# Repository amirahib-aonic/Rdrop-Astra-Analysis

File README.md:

# Rdrop Astra analysis

Three-stage illustrated evaluation: functional review, conservative refinement and complete redesign.

Website: https://amirahib-aonic.github.io/Rdrop-Astra-Analysis/

The four HTML pages use assets/, sources/ and downloads/. Original individual reports are retained in GPT6 Refined/Comparison/ and GPT6 New/Report/.

Hardware files are prototype evidence; automated design checks do not establish flight, functional or thermal qualification.

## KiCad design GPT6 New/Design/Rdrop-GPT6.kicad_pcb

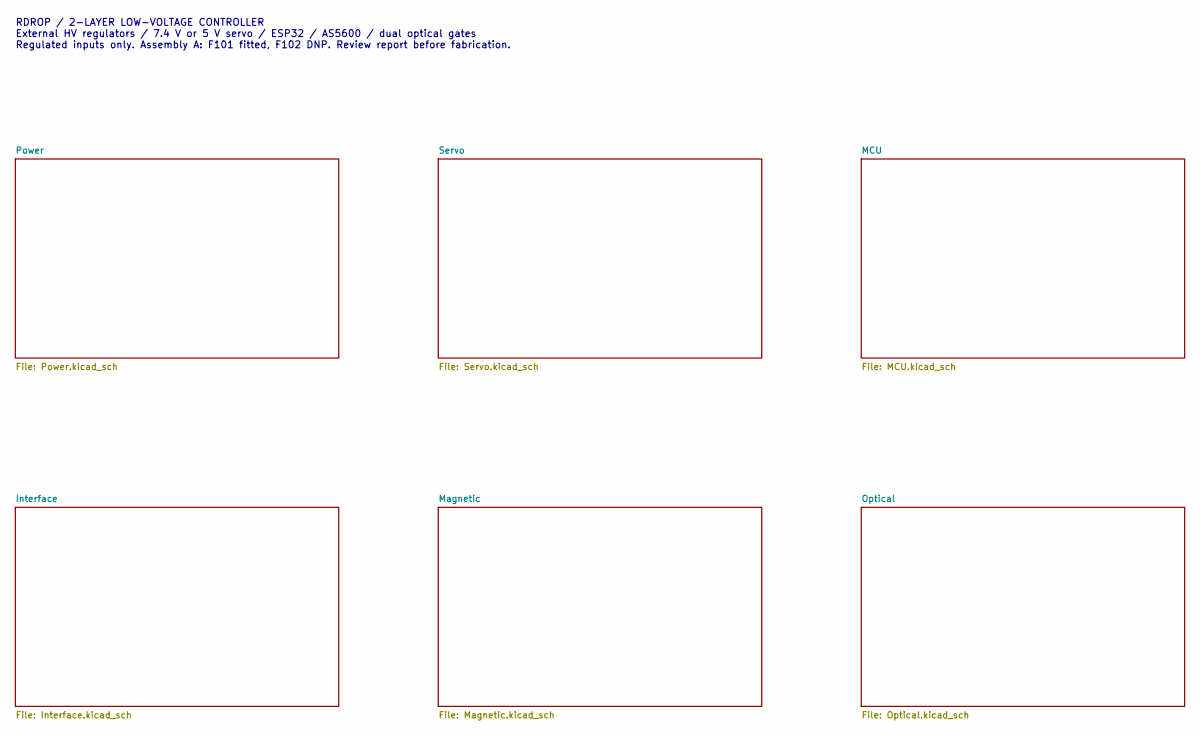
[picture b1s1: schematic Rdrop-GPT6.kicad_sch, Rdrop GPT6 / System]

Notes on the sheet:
RDROP / 2-LAYER LOW-VOLTAGE CONTROLLER External HV regulators / 7.4 V or 5 V servo / ESP32 / AS5600 / dual optical gates Regulated inputs only. Assembly A: F101 fitted, F102 DNP. Review report before fabrication.

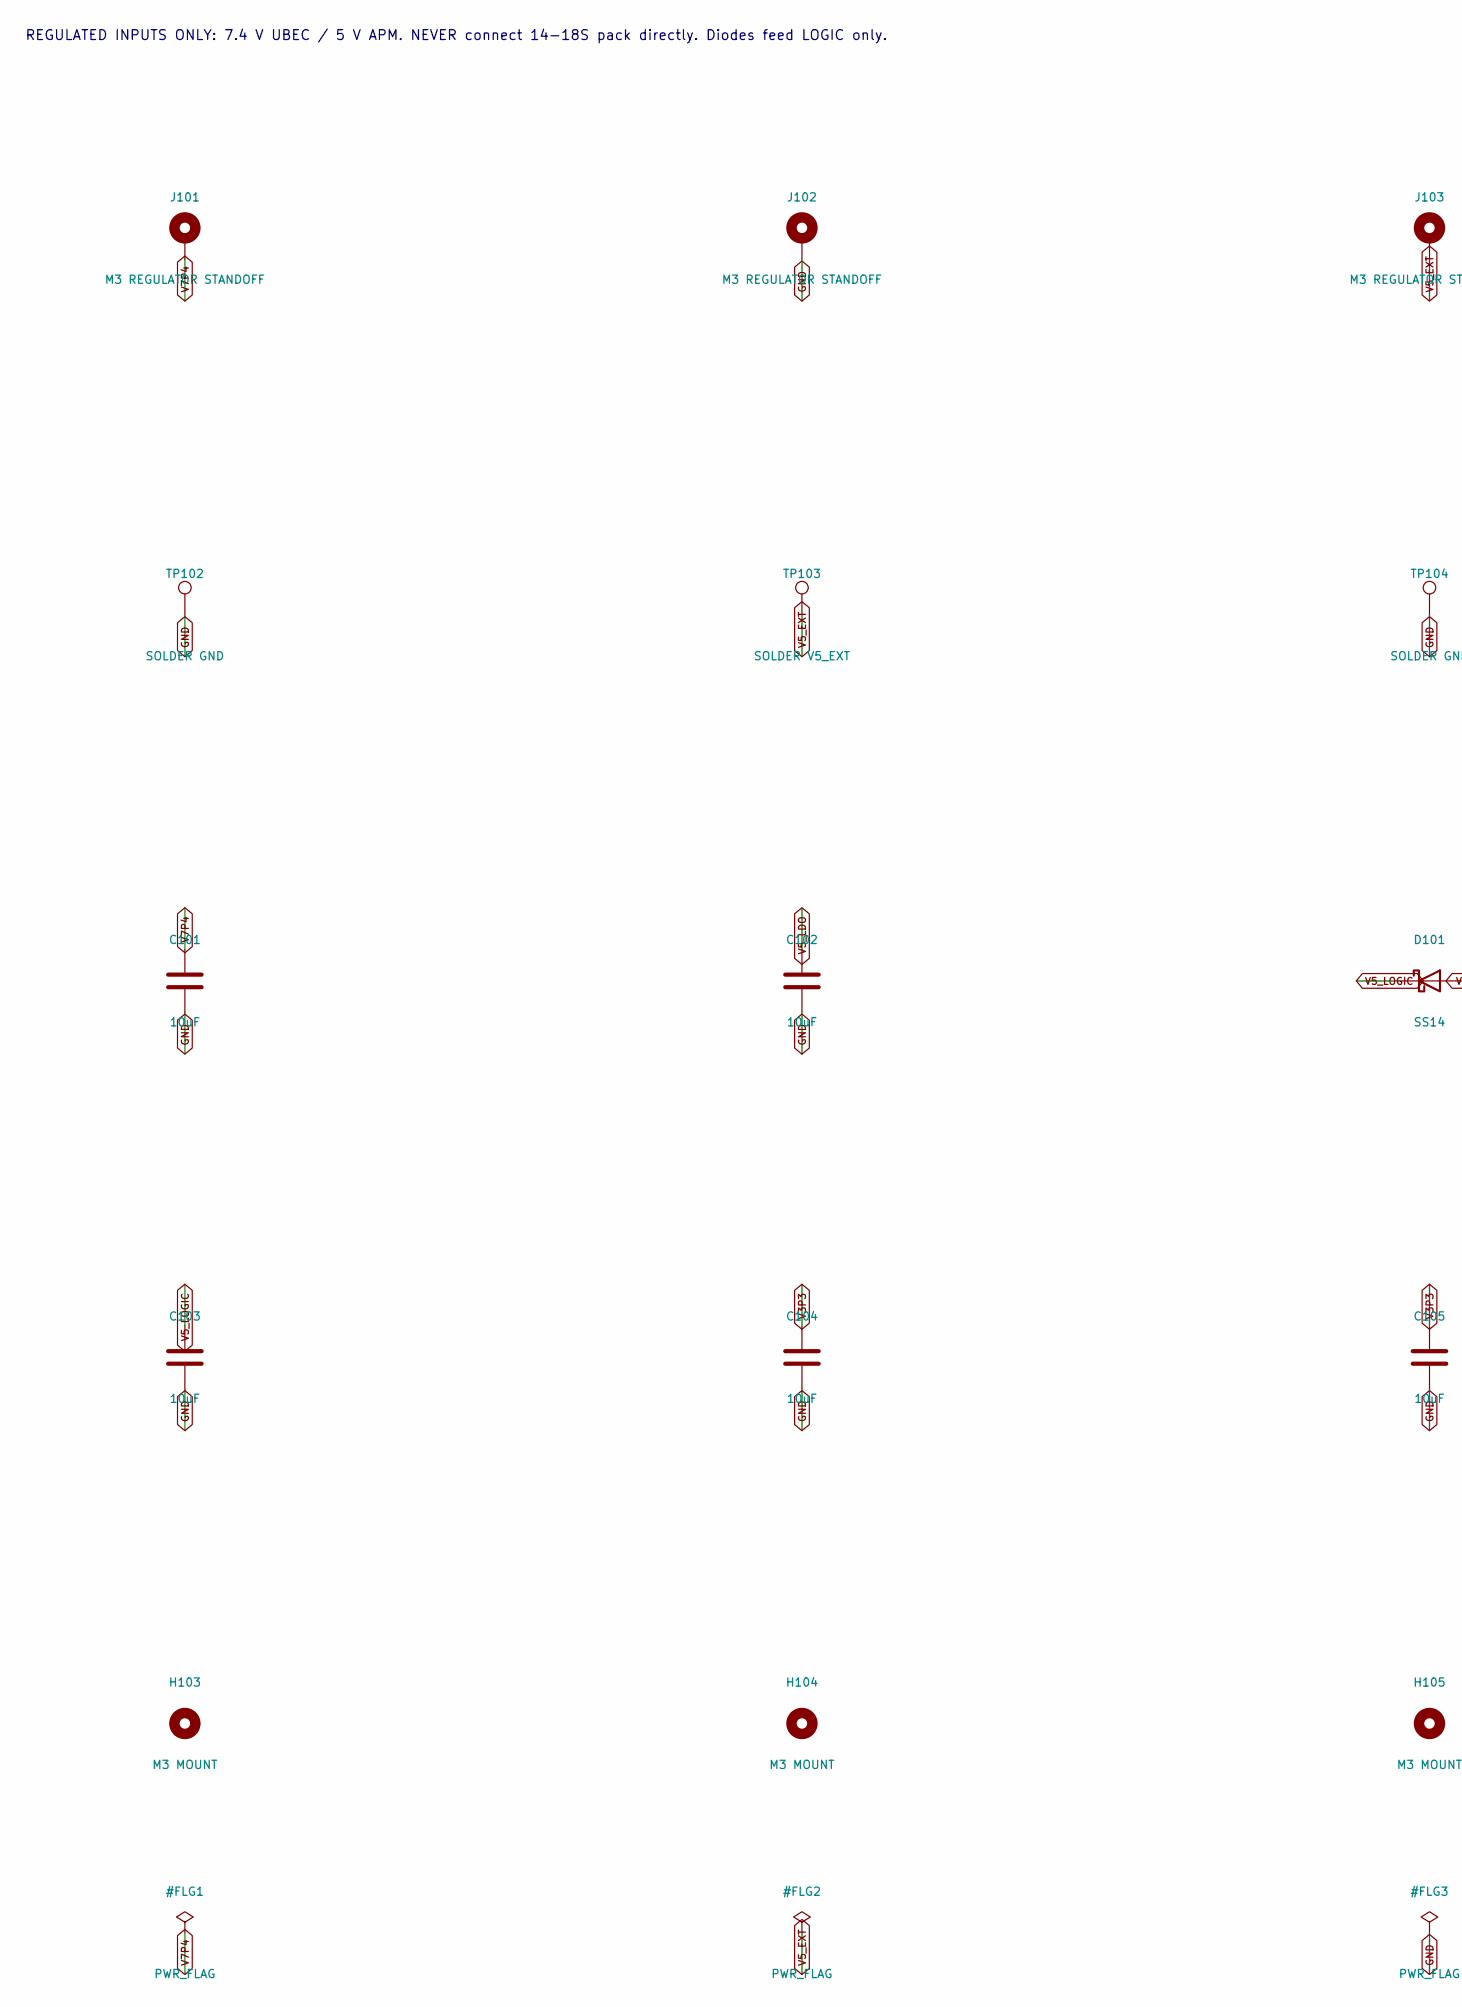
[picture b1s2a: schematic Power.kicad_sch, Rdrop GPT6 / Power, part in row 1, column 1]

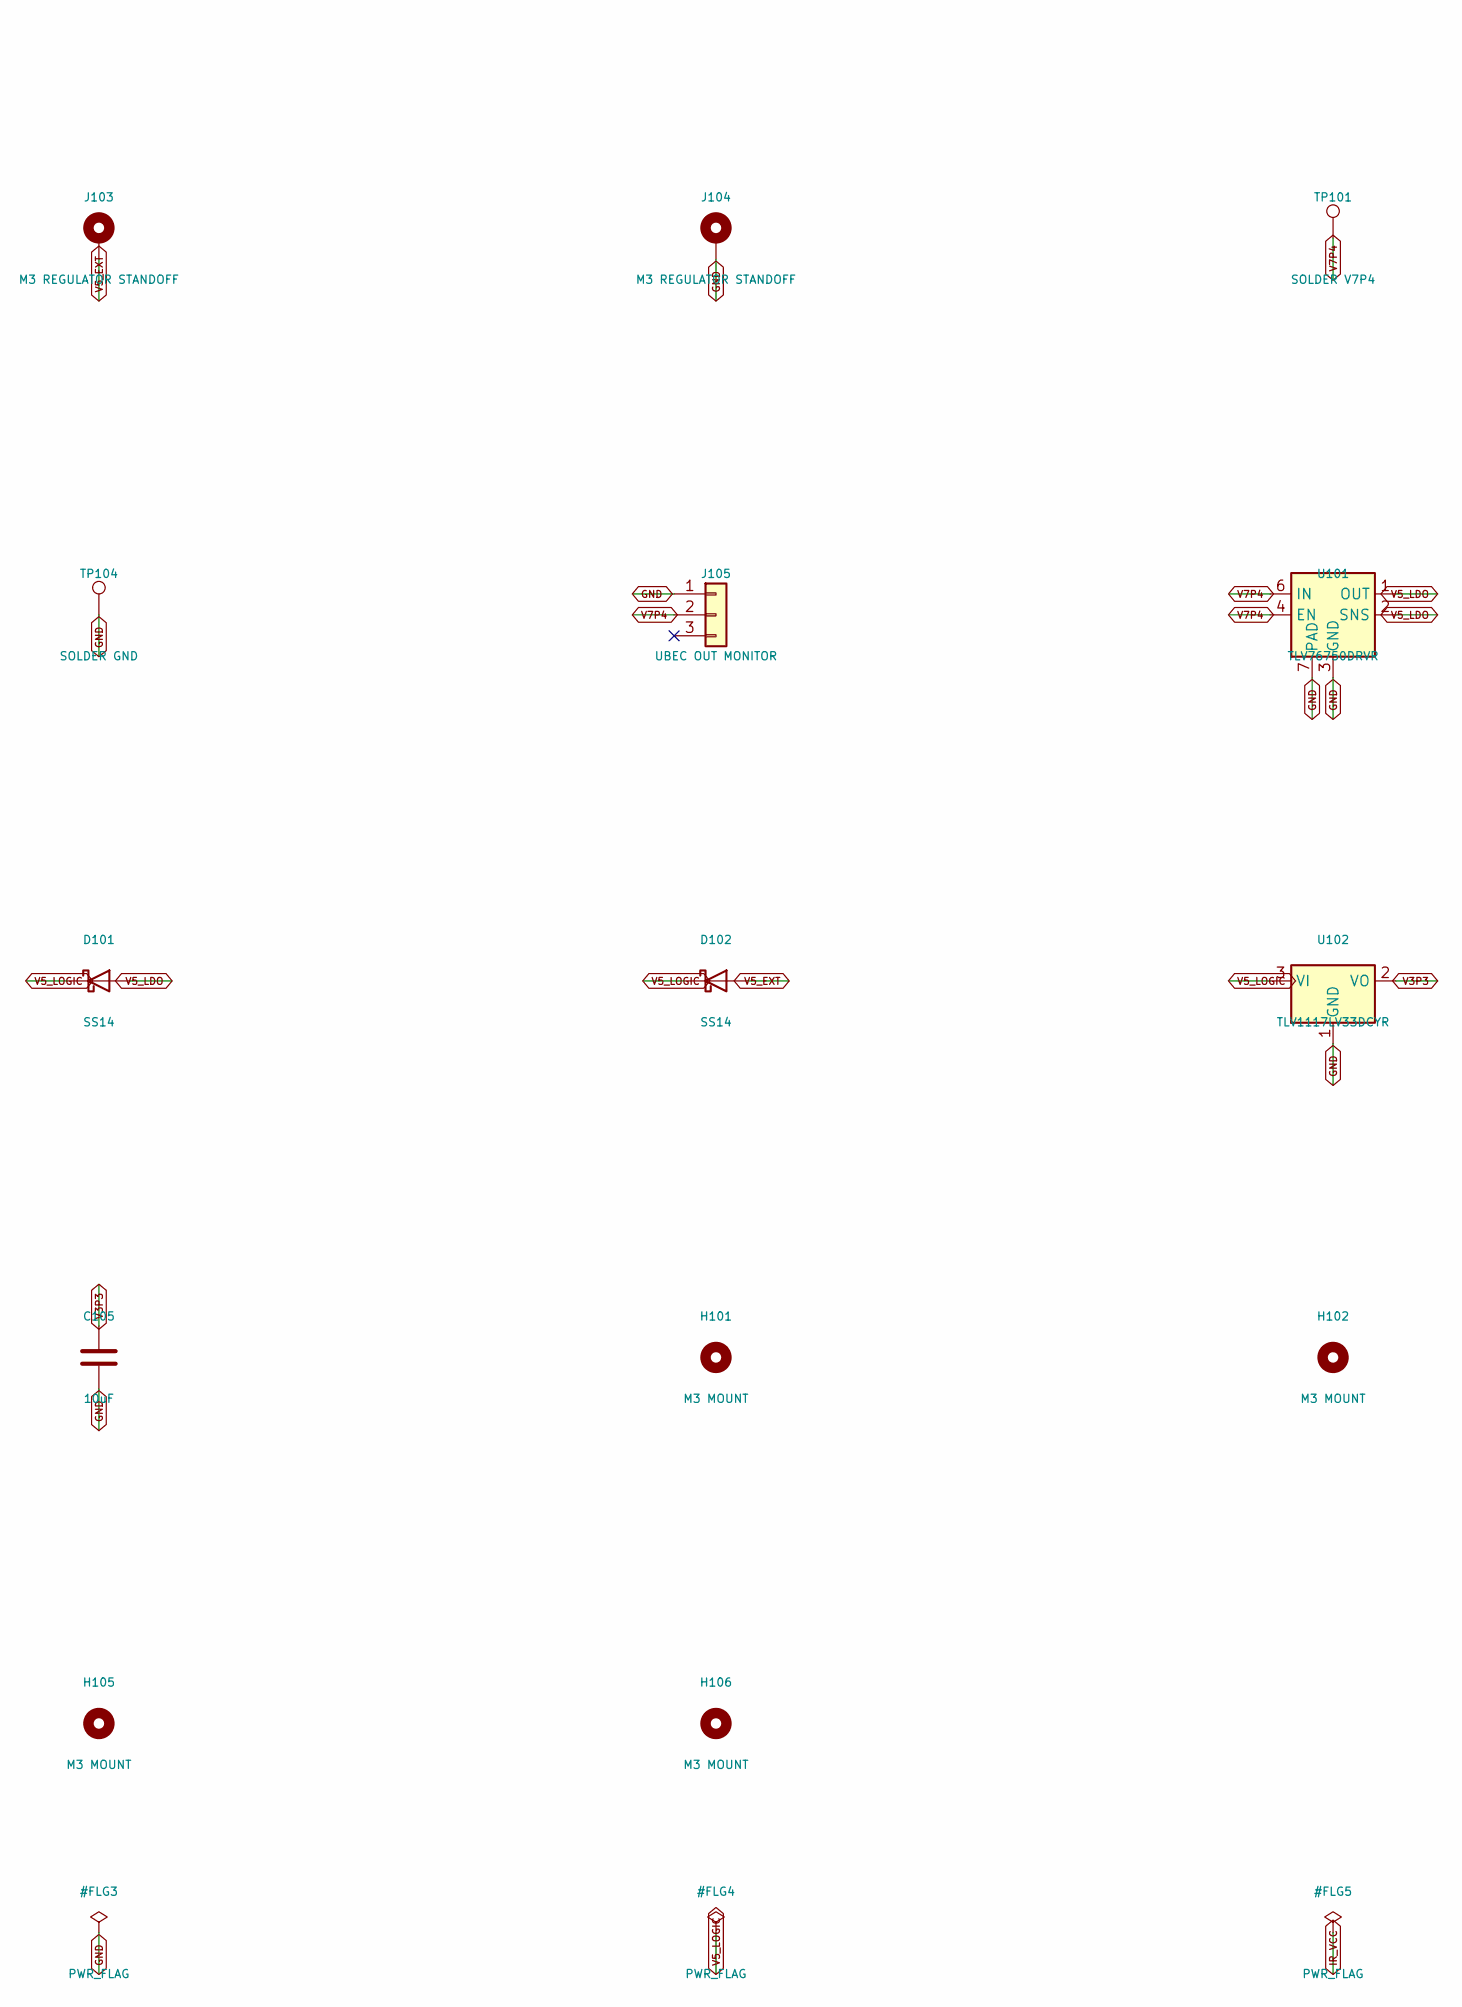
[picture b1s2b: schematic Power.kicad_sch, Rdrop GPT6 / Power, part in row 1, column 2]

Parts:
C101, C102, C103, C104, C105: 10uF; C_0603_1608Metric; MPN GRM188R61C106KAALD
D101, D102: SS14; D_SMA; MPN SS14-E3/61T
H101, H102, H103, H104, H105, H106: M3 MOUNT; MountingHole_3.2mm_M3; MPN M3_HARDWARE
J101, J102, J103, J104: M3 REGULATOR STANDOFF; Mounting_Wuerth_WA-SMSI-M3_H10mm_9774100360; MPN 9774100360R
J105: UBEC OUT MONITOR; PinHeader_1x03_P2.54mm_Vertical; MPN TSW-103-07-G-S
TP101: SOLDER V7P4; TestPoint_Pad_D4.0mm; MPN WIRE_PAD
TP102, TP104: SOLDER GND; TestPoint_Pad_D4.0mm; MPN WIRE_PAD
TP103: SOLDER V5_EXT; TestPoint_Pad_D4.0mm; MPN WIRE_PAD
U101: TLV76750DRVR; WSON-6-1EP_2x2mm_P0.65mm_EP1x1.6mm_ThermalVias; MPN TLV76750DRVR
U102: TLV1117LV33DCYR; SOT-223-3_TabPin2; MPN TLV1117LV33DCYR

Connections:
GND: C101.2, C102.2, C103.2, C104.2, C105.2, J102.1, J104.1, J105.1, TP102.1, TP104.1, U101.3 (GND), U101.5 (GND), U101.7 (PAD), U102.1 (GND); also elsewhere on the board
V3P3: C104.1, C105.1, U102.2 (VO); also elsewhere on the board
V5_EXT: D102.2 (A), J103.1, TP103.1; also elsewhere on the board
V5_LDO: C102.1, D101.2 (A), U101.1 (OUT), U101.2 (SNS)
V5_LOGIC: C103.1, D101.1 (K), D102.1 (K), U102.3 (VI)
V7P4: C101.1, J101.1, J105.2, TP101.1, U101.4 (EN), U101.6 (IN); also elsewhere on the board

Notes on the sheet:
REGULATED INPUTS ONLY: 7.4 V UBEC / 5 V APM. NEVER connect 14-18S pack directly. Diodes feed LOGIC only.

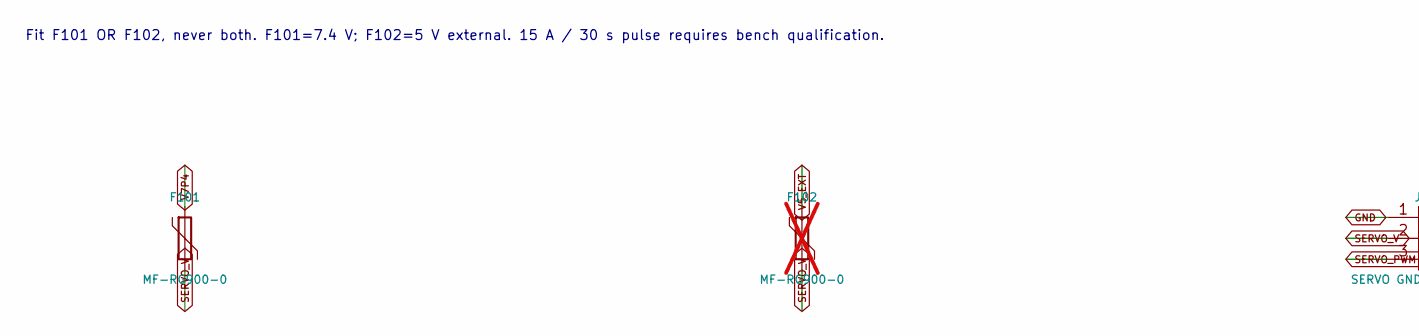
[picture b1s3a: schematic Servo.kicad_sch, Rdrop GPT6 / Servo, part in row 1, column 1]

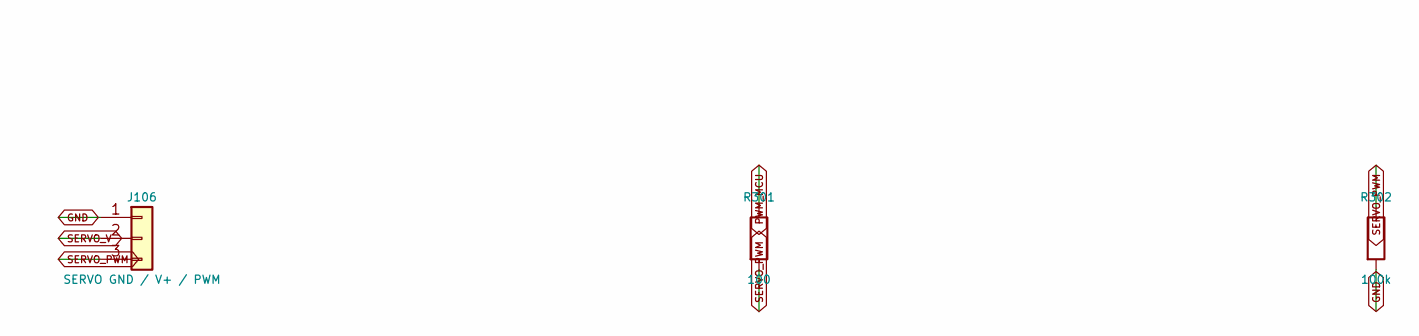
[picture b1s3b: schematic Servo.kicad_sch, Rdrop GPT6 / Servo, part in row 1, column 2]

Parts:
F101: MF-RG900-0; Fuse_Bourns_MF-RG900; MPN MF-RG900-0
F102: MF-RG900-0; Fuse_Bourns_MF-RG900; MPN MF-RG900-0; not fitted
J106: SERVO GND / V+ / PWM; TerminalBlock_Phoenix_MKDS-3-3-5.08_1x03_P5.08mm_Horizontal; MPN 1711738
R301: 100; R_0603_1608Metric; MPN RC0603FR-07100RL
R302: 100k; R_0603_1608Metric; MPN RC0603FR-07100KL

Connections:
GND: J106.1, R302.2; also elsewhere on the board
PWM_MCU: R301.1; also elsewhere on the board
SERVO_PWM: J106.3, R301.2, R302.1
SERVO_V: F101.2, F102.2, J106.2
V5_EXT: F102.1; also elsewhere on the board
V7P4: F101.1; also elsewhere on the board

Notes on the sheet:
Fit F101 OR F102, never both. F101=7.4 V; F102=5 V external. 15 A / 30 s pulse requires bench qualification.

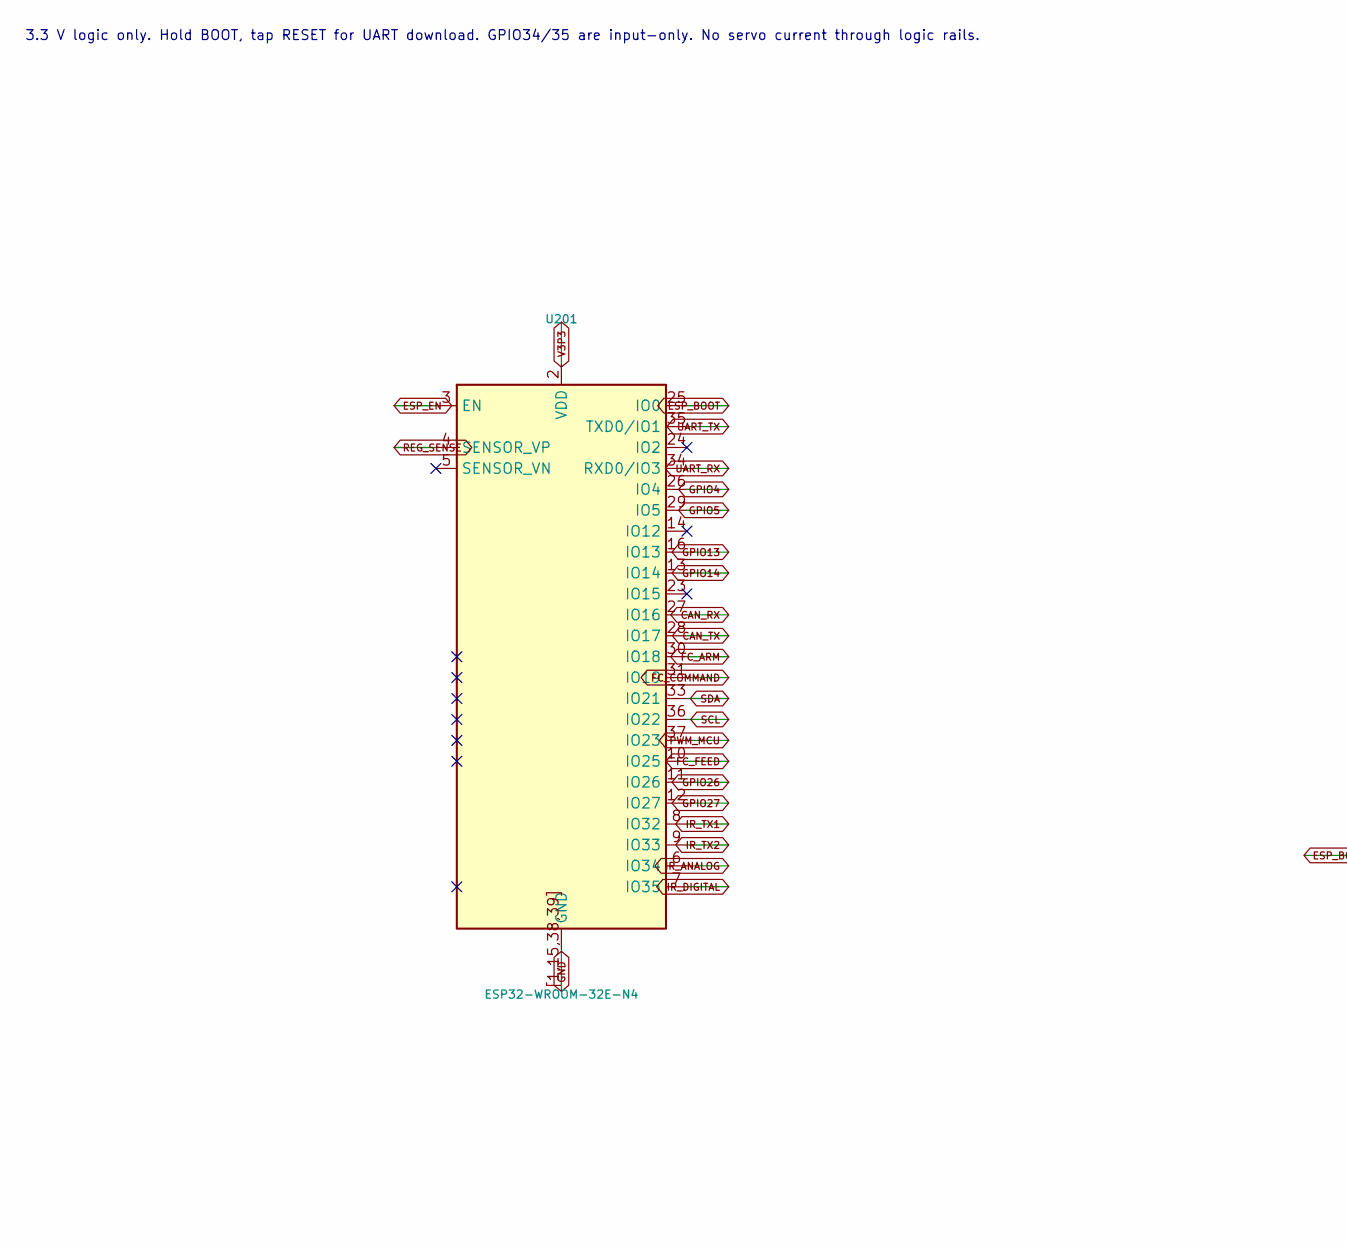
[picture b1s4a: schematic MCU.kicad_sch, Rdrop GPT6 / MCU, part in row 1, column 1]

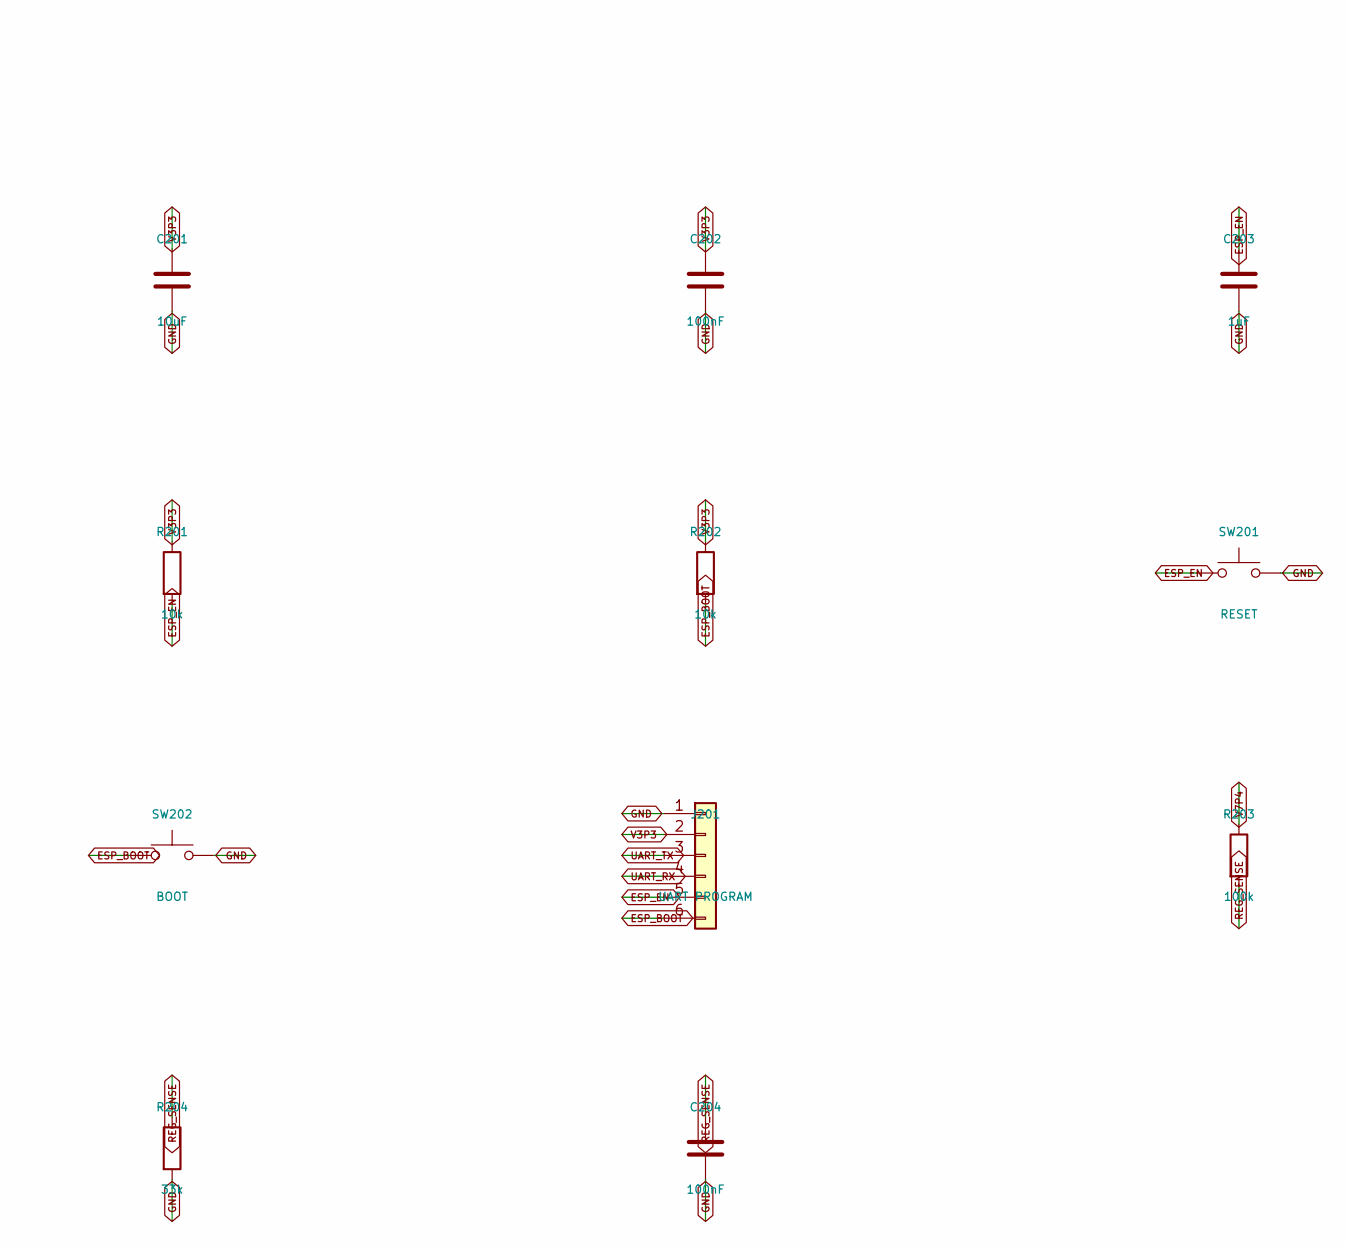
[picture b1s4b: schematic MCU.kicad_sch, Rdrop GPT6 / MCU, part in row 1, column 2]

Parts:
C201: 10uF; C_0603_1608Metric; MPN GRM188R61C106KAALD
C202, C204: 100nF; C_0603_1608Metric; MPN GRM188R71H104KA93D
C203: 1uF; C_0603_1608Metric; MPN GRM188R61E105KA12D
J201: UART PROGRAM; PinHeader_1x06_P2.54mm_Vertical; MPN TSW-106-07-G-S
R201, R202: 10k; R_0603_1608Metric; MPN RC0603FR-0710KL
R203: 100k; R_0603_1608Metric; MPN RC0603FR-07100KL
R204: 33k; R_0603_1608Metric; MPN RC0603FR-0733KL
SW201: RESET; SW_SPST_TL3342; MPN TL3342F160QG
SW202: BOOT; SW_SPST_TL3342; MPN TL3342F160QG
U201: ESP32-WROOM-32E-N4; ESP32-WROOM-32E; MPN ESP32-WROOM-32E-N4

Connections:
CAN_RX: U201.27 (IO16); also elsewhere on the board
CAN_TX: U201.28 (IO17); also elsewhere on the board
ESP_BOOT: J201.6, R202.2, SW202.1, U201.25 (IO0)
ESP_EN: C203.1, J201.5, R201.2, SW201.1, U201.3 (EN)
FC_ARM: U201.30 (IO18); also elsewhere on the board
FC_COMMAND: U201.31 (IO19); also elsewhere on the board
FC_FEED: U201.10 (IO25); also elsewhere on the board
GND: C201.2, C202.2, C203.2, C204.2, J201.1, R204.2, SW201.2, SW202.2, U201.1, U201.15, U201.38, U201.39, U201.[1,15,38,39] (GND); also elsewhere on the board
GPIO4: U201.26 (IO4); also elsewhere on the board
GPIO5: U201.29 (IO5); also elsewhere on the board
GPIO13: U201.16 (IO13); also elsewhere on the board
GPIO14: U201.13 (IO14); also elsewhere on the board
GPIO26: U201.11 (IO26); also elsewhere on the board
GPIO27: U201.12 (IO27); also elsewhere on the board
IR_ANALOG: U201.6 (IO34); also elsewhere on the board
IR_DIGITAL: U201.7 (IO35); also elsewhere on the board
IR_TX1: U201.8 (IO32); also elsewhere on the board
IR_TX2: U201.9 (IO33); also elsewhere on the board
PWM_MCU: U201.37 (IO23); also elsewhere on the board
REG_SENSE: C204.1, R203.2, R204.1, U201.4 (SENSOR_VP); also elsewhere on the board
SCL: U201.36 (IO22); also elsewhere on the board
SDA: U201.33 (IO21); also elsewhere on the board
UART_RX: J201.4, U201.34 (RXD0/IO3); also elsewhere on the board
UART_TX: J201.3, U201.35 (TXD0/IO1); also elsewhere on the board
V3P3: C201.1, C202.1, J201.2, R201.1, R202.1, U201.2 (VDD); also elsewhere on the board
V7P4: R203.1; also elsewhere on the board

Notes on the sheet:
3.3 V logic only. Hold BOOT, tap RESET for UART download. GPIO34/35 are input-only. No servo current through logic rails.

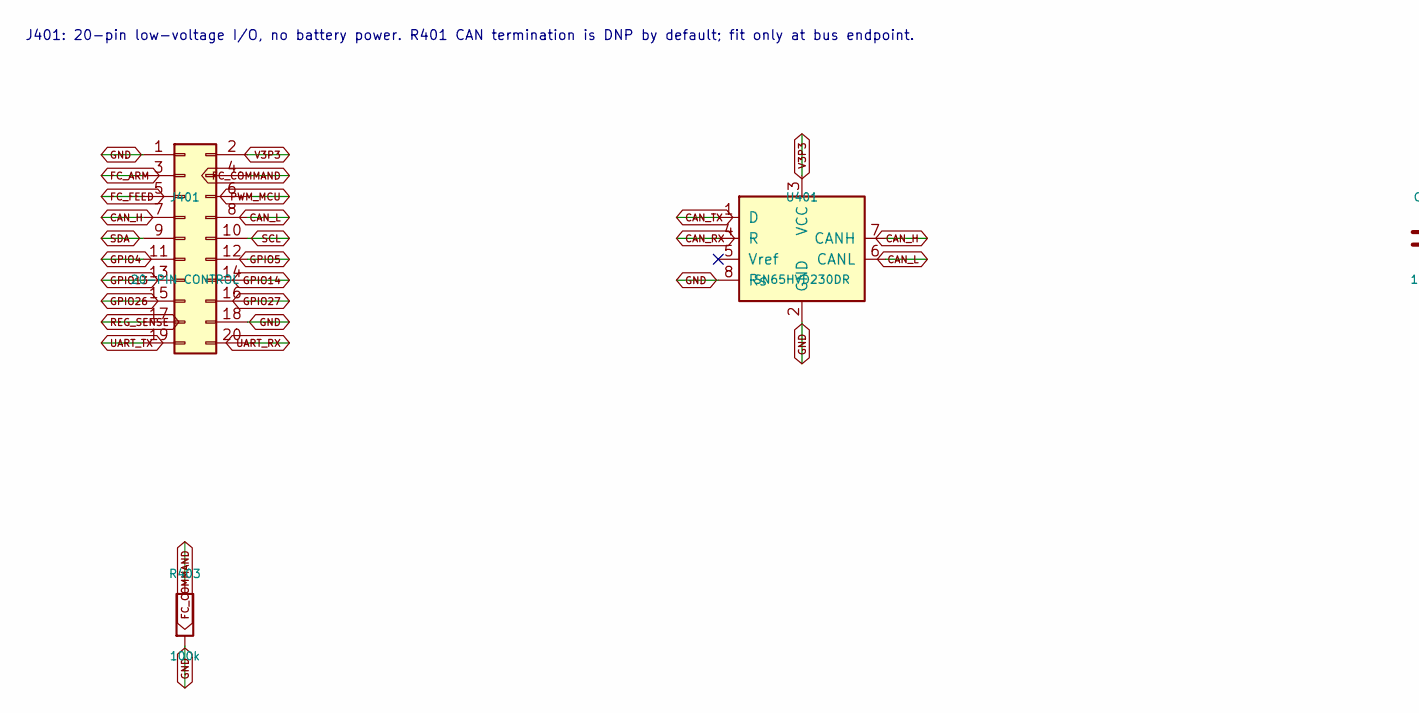
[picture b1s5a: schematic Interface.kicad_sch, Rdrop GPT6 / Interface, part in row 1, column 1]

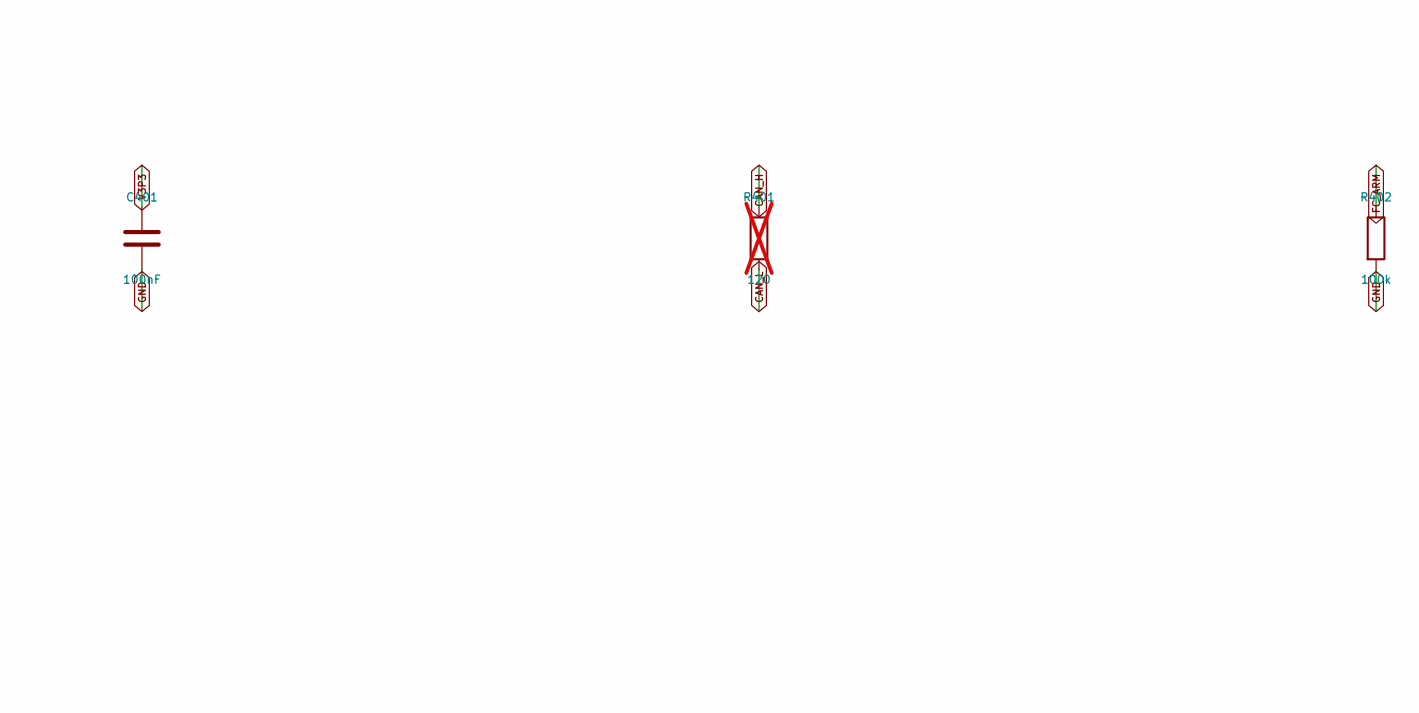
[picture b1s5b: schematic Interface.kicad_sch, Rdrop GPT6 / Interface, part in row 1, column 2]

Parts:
C401: 100nF; C_0603_1608Metric; MPN GRM188R71H104KA93D
J401: 20-PIN CONTROL; PinHeader_2x10_P2.54mm_Vertical; MPN TSW-110-07-G-D
R401: 120; R_0603_1608Metric; MPN RC0603FR-07120RL; not fitted
R402, R403: 100k; R_0603_1608Metric; MPN RC0603FR-07100KL
U401: SN65HVD230DR; SOIC-8_3.9x4.9mm_P1.27mm; MPN SN65HVD230DR

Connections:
CAN_H: J401.7, R401.1, U401.7 (CANH)
CAN_L: J401.8, R401.2, U401.6 (CANL)
CAN_RX: U401.4 (R); also elsewhere on the board
CAN_TX: U401.1 (D); also elsewhere on the board
FC_ARM: J401.3, R402.1; also elsewhere on the board
FC_COMMAND: J401.4, R403.1; also elsewhere on the board
FC_FEED: J401.5; also elsewhere on the board
GND: C401.2, J401.1, J401.18, R402.2, R403.2, U401.2 (GND), U401.8 (Rs); also elsewhere on the board
GPIO4: J401.11; also elsewhere on the board
GPIO5: J401.12; also elsewhere on the board
GPIO13: J401.13; also elsewhere on the board
GPIO14: J401.14; also elsewhere on the board
GPIO26: J401.15; also elsewhere on the board
GPIO27: J401.16; also elsewhere on the board
PWM_MCU: J401.6; also elsewhere on the board
REG_SENSE: J401.17; also elsewhere on the board
SCL: J401.10; also elsewhere on the board
SDA: J401.9; also elsewhere on the board
UART_RX: J401.20; also elsewhere on the board
UART_TX: J401.19; also elsewhere on the board
V3P3: C401.1, J401.2, U401.3 (VCC); also elsewhere on the board

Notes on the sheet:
J401: 20-pin low-voltage I/O, no battery power. R401 CAN termination is DNP by default; fit only at bus endpoint.

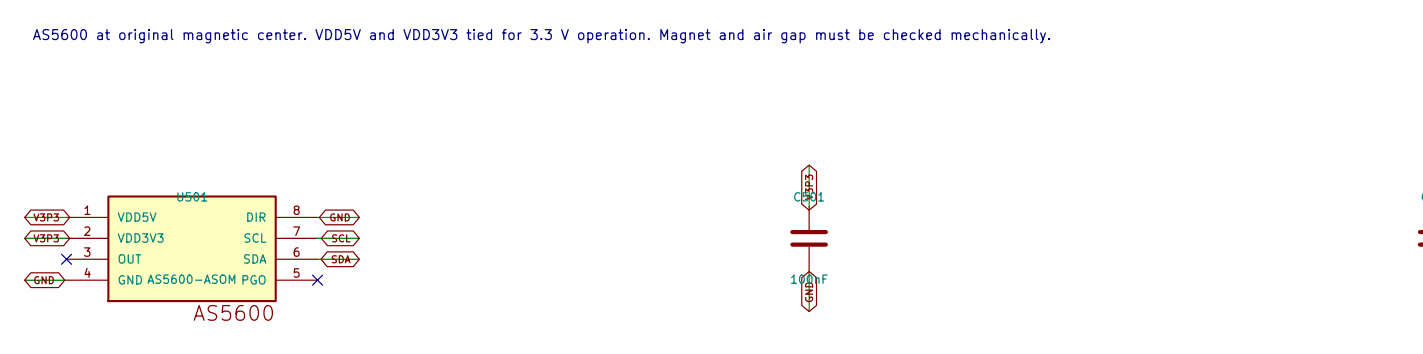
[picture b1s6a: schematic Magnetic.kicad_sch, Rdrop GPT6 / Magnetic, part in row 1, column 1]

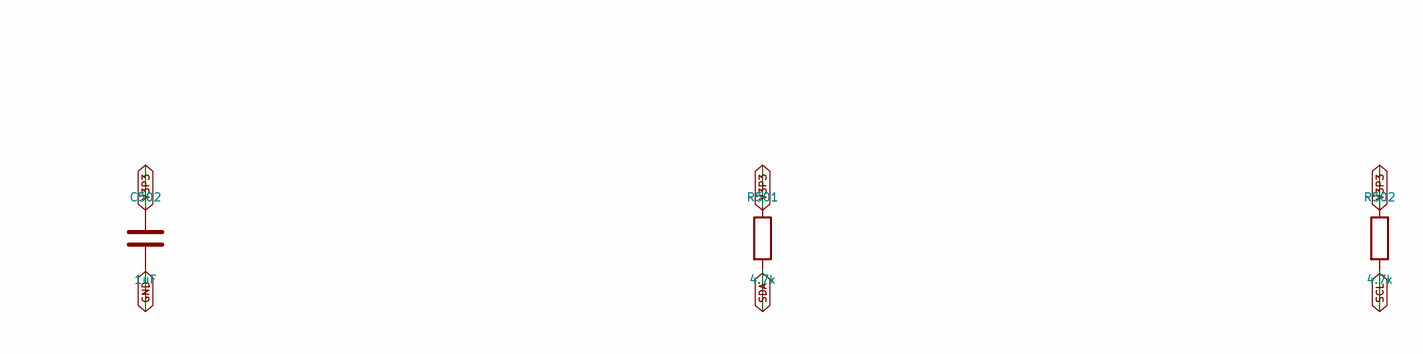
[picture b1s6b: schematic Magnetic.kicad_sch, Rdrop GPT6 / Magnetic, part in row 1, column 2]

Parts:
C501: 100nF; C_0603_1608Metric; MPN GRM188R71H104KA93D
C502: 1uF; C_0603_1608Metric; MPN GRM188R61E105KA12D
R501, R502: 4.7k; R_0603_1608Metric; MPN RC0603FR-074K7L
U501: AS5600-ASOM; SOIC-8_3.9x4.9mm_P1.27mm; MPN AS5600-ASOM

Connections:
GND: C501.2, C502.2, U501.4 (GND), U501.8 (DIR); also elsewhere on the board
SCL: R502.2, U501.7 (SCL); also elsewhere on the board
SDA: R501.2, U501.6 (SDA); also elsewhere on the board
V3P3: C501.1, C502.1, R501.1, R502.1, U501.1 (VDD5V), U501.2 (VDD3V3); also elsewhere on the board

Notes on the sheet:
AS5600 at original magnetic center. VDD5V and VDD3V3 tied for 3.3 V operation. Magnet and air gap must be checked mechanically.
